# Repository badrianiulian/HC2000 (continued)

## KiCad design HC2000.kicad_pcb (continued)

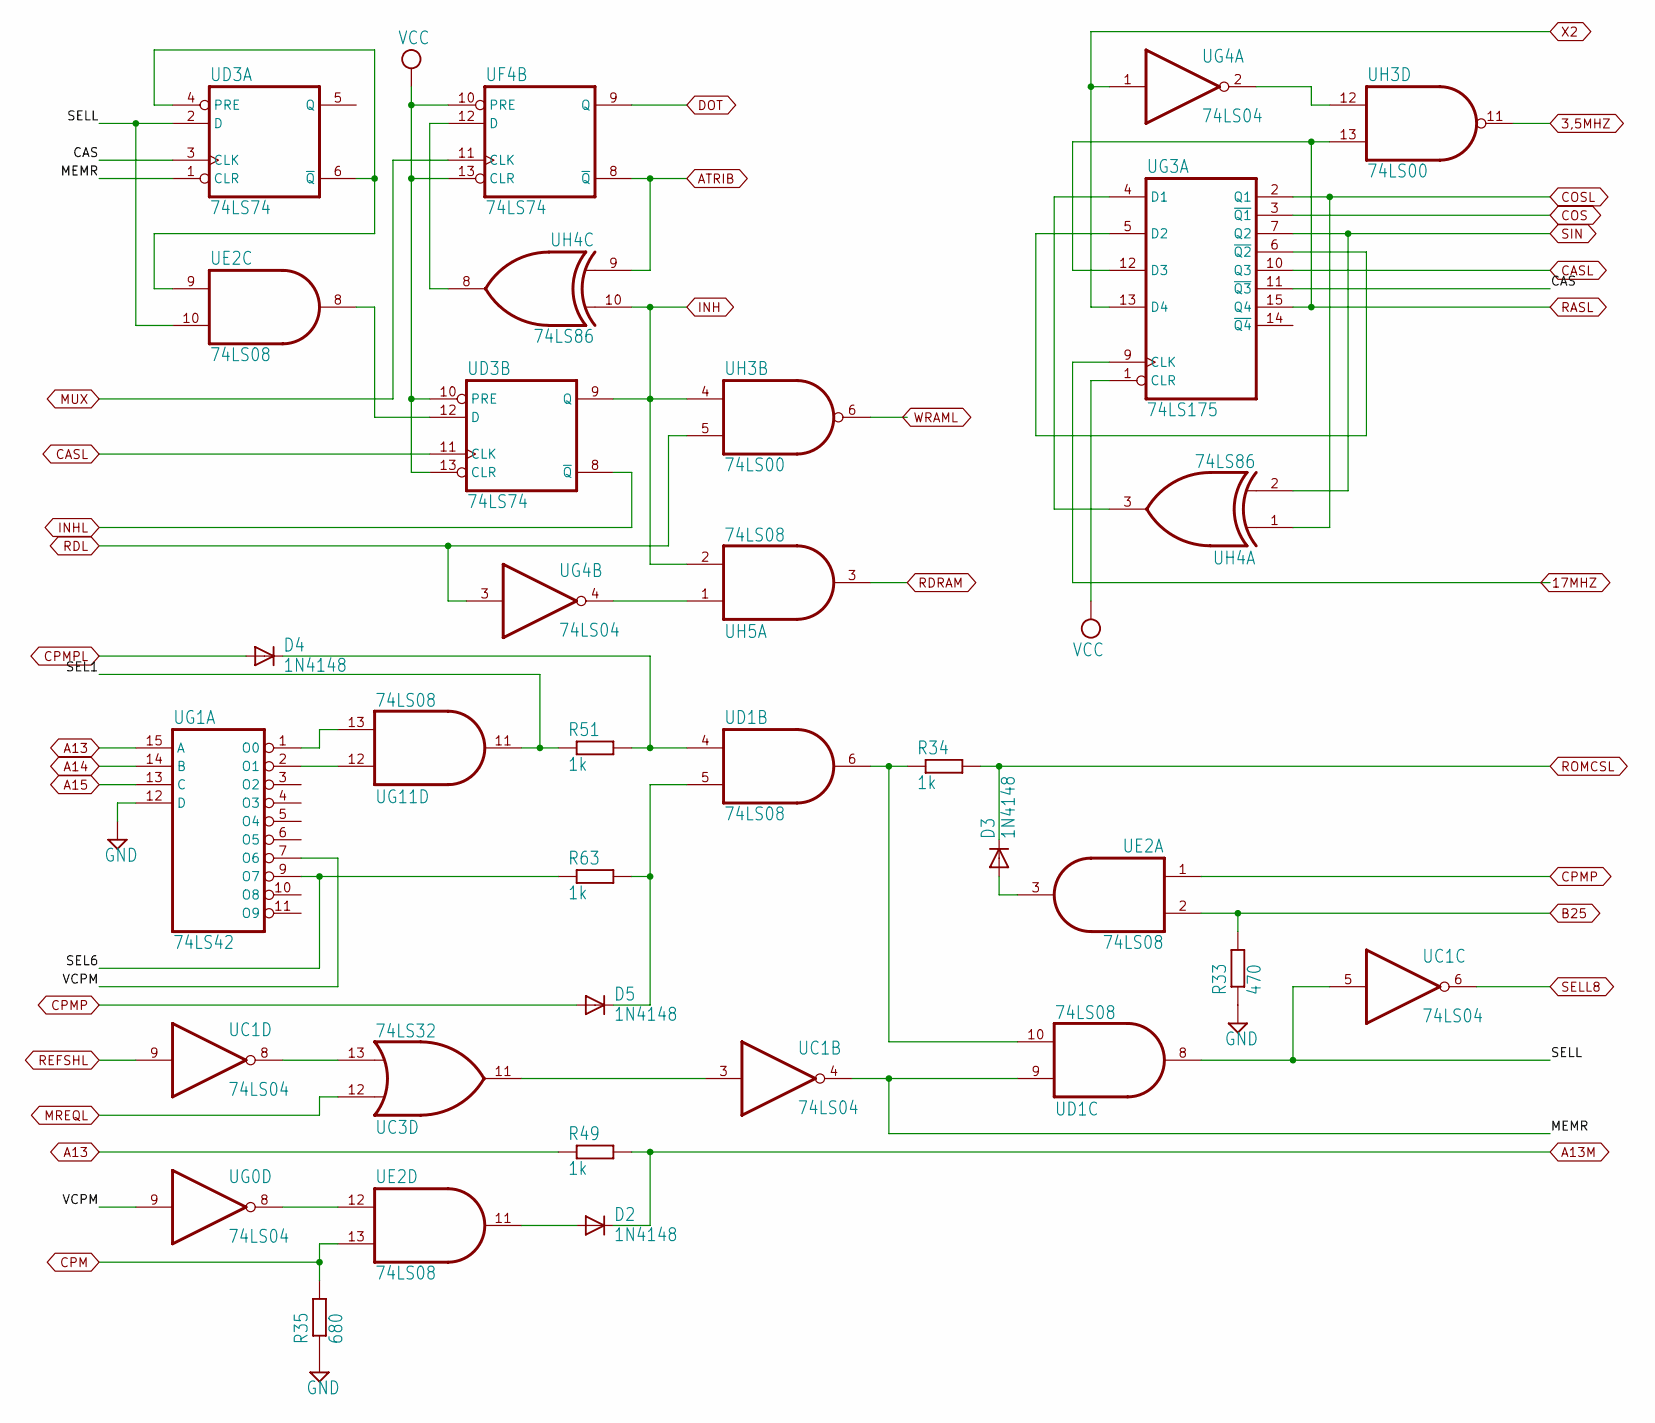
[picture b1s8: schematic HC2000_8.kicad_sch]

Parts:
D2, D3, D4, D5: 1N4148; DO35-10
R33: 470; 0204_7
R34, R49, R51, R63: 1k; 0204_7
R35: 680; 0204_7
UC1: 74LS04; DIL14
UC3: 74LS32; DIL14
UD1: 74LS08; DIL14
UD3: 74LS74; DIL14
UE2: 74LS08; DIL14
UF4: 74LS74; DIL14
UG0, UG4: 74LS04; DIL14
UG1: 74LS42; DIL16
UG3: 74LS175; DIL16
UG11: 74LS08; DIL14
UH3: 74LS00; DIL14
UH4: 74LS86; DIL14
UH5: 74LS08; DIL14

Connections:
3,5MHZ: UH3.11 (O); also elsewhere on the board
17MHZ: UG3.9 (CLK); also elsewhere on the board
/HC2000_8/CAS: UD3.3 (CLK), UG3.11 (~Q3)
/HC2000_8/MEMR: UC1.4 (O), UD1.9 (I0), UD3.1 (CLR)
/HC2000_8/SEL1: R51.1, UG11.11 (O)
/HC2000_8/SEL6: R63.1, UG1.9 (O7)
/HC2000_8/SELL: UC1.5 (I), UD1.8 (O), UD3.2 (D), UE2.10 (I1)
/HC2000_8/VCPM: UG0.9 (I), UG1.7 (O6)
A13M: D2.C, R49.2; also elsewhere on the board
A15: UG1.13 (C); also elsewhere on the board
ATRIB: UF4.8 (~Q), UH4.9 (I0); also elsewhere on the board
B25: R33.2, UE2.2 (I1); also elsewhere on the board
CASL: UD3.11 (CLK), UG3.10 (Q3); also elsewhere on the board
CPM: R35.2, UE2.13 (I1); also elsewhere on the board
CPMP: D5.A, UE2.1 (I0); also elsewhere on the board
CPMPL: D4.A; also elsewhere on the board
DOT: UF4.9 (Q); also elsewhere on the board
INH: UD3.9 (Q), UH3.4 (I0), UH4.10 (I1), UH5.2 (I1); also elsewhere on the board
INHL: UD3.8 (~Q); also elsewhere on the board
MUX: UF4.11 (CLK); also elsewhere on the board
unnamed: UC1.3 (I), UC3.11 (O)
unnamed: UC1.8 (O), UC3.13 (I1)
unnamed: D4.C, R51.2, UD1.4 (I0)
unnamed: D5.C, R63.2, UD1.5 (I1)
unnamed: R34.1, UD1.6 (O), UD1.10 (I1)
unnamed: UD3.4 (PRE), UD3.6 (~Q), UE2.9 (I0)
unnamed: UD3.12 (D), UE2.8 (O)
unnamed: D3.A, UE2.3 (O)
unnamed: UE2.12 (I0), UG0.8 (O)
unnamed: D2.A, UE2.11 (O)
unnamed: UF4.12 (D), UH4.8 (O)
unnamed: UG3.4 (D1), UH4.3 (O)
unnamed: UG3.5 (D2), UG3.6 (~Q2)
unnamed: UG4.2 (O), UH3.12 (I0)
unnamed: UG4.4 (O), UH5.1 (I0)
unnamed: UG1.2 (O1), UG11.12 (I0)
unnamed: UG1.1 (O0), UG11.13 (I1)
RASL: UG3.12 (D3), UG3.15 (Q4), UH3.13 (I1); also elsewhere on the board
RDL: UG4.3 (I), UH3.5 (I1); also elsewhere on the board
RDRAM: UH5.3 (O); also elsewhere on the board
REFSHL: UC1.9 (I); also elsewhere on the board
SELL8: UC1.6 (O); also elsewhere on the board
WRAML: UH3.6 (O); also elsewhere on the board
X2: UG3.13 (D4), UG4.1 (I); also elsewhere on the board

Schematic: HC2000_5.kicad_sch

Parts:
C6: -; C025-030X050
R36: 100; 0204_7
UC4, UC5: 74LS257; DIL16
UC7: 74LS244; DIL20
UD5: 74LS257; DIL16
UD7: TMM41464AP-12; DIL18
UE2: 74LS08; DIL14
UE3: 74LS32; DIL14
UE7: TMM41464AP-12; DIL18
UF3: 74LS175; DIL16
UG7: 74LS257; DIL16

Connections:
/HC2000_5/CVS: UD5.14 (4A), UF3.7 (Q2)
/HC2000_5/VMA0: UC5.4 (1Y), UD7.14 (A0), UE7.14 (A0), UG7.9 (3Y)
/HC2000_5/VMA1: UC5.9 (3Y), UD7.13 (A1), UE7.13 (A1), UG7.4 (1Y)
/HC2000_5/VMA2: UC5.12 (4Y), UD7.12 (A2), UE7.12 (A2), UG7.7 (2Y)
/HC2000_5/VMA3: UC5.7 (2Y), UD7.11 (A3), UE7.11 (A3), UG7.12 (4Y)
/HC2000_5/VMA4: UC4.9 (3Y), UD5.9 (3Y), UD7.8 (A4), UE7.8 (A4)
/HC2000_5/VMA5: UC4.7 (2Y), UD5.4 (1Y), UD7.7 (A5), UE7.7 (A5)
/HC2000_5/VMA6: UC4.4 (1Y), UD5.7 (2Y), UD7.6 (A6), UE7.6 (A6)
/HC2000_5/VMA7: UC4.12 (4Y), UD5.12 (4Y), UD7.10 (A7), UE7.10 (A7)
A: UD5.13 (4B); also elsewhere on the board
A13M: UC4.2 (1A); also elsewhere on the board
A15: UC4.14 (4A); also elsewhere on the board
B: UD5.6 (2B); also elsewhere on the board
C: UD5.11 (3A); also elsewhere on the board
CASL: UD7.16 (~CAS), UE7.16 (~CAS); also elsewhere on the board
CPMP: UF3.3 (~Q1); also elsewhere on the board
CPMPL: UF3.2 (Q1); also elsewhere on the board
D: UD5.3 (1B); also elsewhere on the board
D4: UC7.17 (A4); also elsewhere on the board
D5: UC7.15 (A3); also elsewhere on the board
D6: UC7.11 (A1); also elsewhere on the board
D7: UC7.13 (A2); also elsewhere on the board
IG3: UG7.2 (1A); also elsewhere on the board
IG4: UG7.5 (2A); also elsewhere on the board
IG5: UG7.11 (3A); also elsewhere on the board
INH: UD5.15 (G), UG7.15 (G); also elsewhere on the board
INHL: UC4.15 (G), UC5.15 (G); also elsewhere on the board
MUX: UC4.1 (~A/B), UC5.1 (~A/B), UD5.1 (~A/B), UE2.6 (O), UG7.1 (~A/B); also elsewhere on the board
unnamed: C6.1, R36.1, UE2.4 (I0), UE2.5 (I1)
unnamed: UE3.4 (I0), UF3.15 (Q4)
unnamed: UE3.6 (O), UF3.9 (CLK)
OUT7EL: UE3.5 (I1); also elsewhere on the board
RASL: R36.2, UD7.5 (~RAS), UE7.5 (~RAS); also elsewhere on the board
RESETL: UF3.1 (CLR); also elsewhere on the board
VD0: UC7.16 (Y2), UD7.2 (I/O1); also elsewhere on the board
VD1: UC7.14 (Y3), UD7.3 (I/O2); also elsewhere on the board
VD2: UC7.12 (Y4), UD7.15 (I/O3); also elsewhere on the board
VD3: UC7.18 (Y1), UD7.17 (I/O4); also elsewhere on the board
VD4: UC7.3 (Y4), UE7.2 (I/O1); also elsewhere on the board
VD5: UC7.5 (Y3), UE7.3 (I/O2); also elsewhere on the board
VD6: UC7.9 (Y1), UE7.15 (I/O3); also elsewhere on the board
VD7: UC7.7 (Y2), UE7.17 (I/O4); also elsewhere on the board
WRAML: UC7.1 (G), UC7.19 (G), UD7.4 (~WE), UE7.4 (~WE); also elsewhere on the board
X3Y7: UD5.2 (1A); also elsewhere on the board
X5: UG7.10 (3B); also elsewhere on the board
X6: UG7.3 (1B); also elsewhere on the board
X7: UG7.6 (2B); also elsewhere on the board
X8: UG7.13 (4B); also elsewhere on the board
X9: UD5.10 (3B); also elsewhere on the board

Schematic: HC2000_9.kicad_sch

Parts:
R26, R42, R45: -; 0204_7
R28, R37, R38, R40, R41: 1k; 0204_7
UA11: 74LS06; DIL14
UB12: 74LS153; DIL16
UC12: 74LS175; DIL16
UD11: 74LS14; DIL14
UE8: 8272 or D765AC-2; DIL40
UG11: 74LS08; DIL14

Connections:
CLK8272: UC12.9 (CLK), UE8.19 (CLK); also elsewhere on the board
CS8272: UE8.4 (NCS); also elsewhere on the board
D4: UE8.10 (D4); also elsewhere on the board
D5: UE8.11 (D5); also elsewhere on the board
D6: UE8.12 (D6); also elsewhere on the board
D7: UE8.13 (D7); also elsewhere on the board
DIR: UA11.8 (O); also elsewhere on the board
DWIN: UE8.22 (DW); also elsewhere on the board
FRDATA: UE8.23 (RDDATA); also elsewhere on the board
unnamed: UA11.3 (I), UC12.2 (Q1)
unnamed: UA11.5 (I), UC12.1 (CLR), UE8.25 (WE)
unnamed: UA11.9 (I), UB12.9 (2Y)
unnamed: UA11.11 (I), UG11.8 (O)
unnamed: UA11.13 (I), UE8.27 (HDSEL)
unnamed: UB12.6 (1C0), UC12.5 (D2), UC12.10 (Q3)
unnamed: UB12.5 (1C1), UC12.12 (D3), UC12.15 (Q4)
unnamed: UB12.4 (1C2), UC12.7 (Q2)
unnamed: UB12.7 (1Y), UC12.4 (D1)
unnamed: UB12.10 (2C0), UB12.11 (2C1), UB12.12 (2C2), UB12.13 (2C3), UE8.38 (LCT/DIR)
unnamed: UB12.14 (A), UE8.32 (PS0)
unnamed: UB12.2 (B), UE8.31 (PS1)
unnamed: UC12.13 (D4), UE8.30 (WRDATA)
unnamed: UD11.8 (O), UE8.34 (WP/TS)
unnamed: UD11.6 (O), UG11.4 (I0)
unnamed: UE8.33 (FLT/TRK00), UG11.6 (O)
unnamed: UE8.37 (FR/STP), UG11.10 (I1)
unnamed: R38.1, UE8.15 (NDACK)
unnamed: UE8.39 (NRW/SEEK), UG11.5 (I1), UG11.9 (I0)
unnamed: R37.1, UE8.35 (RDY)
PROT: R26.2, R28.1, UD11.9 (I); also elsewhere on the board
RD8272: UE8.2 (NRD); also elsewhere on the board
RES8272: UE8.1 (RST); also elsewhere on the board
SIDE: UA11.12 (O); also elsewhere on the board
STEP: UA11.10 (O); also elsewhere on the board
TC: UE8.16 (TC); also elsewhere on the board
TRACK0: R40.1, R45.2, UD11.5 (I); also elsewhere on the board
VCO: UE8.24 (VCO); also elsewhere on the board
WR8272: UE8.3 (NWR); also elsewhere on the board
WRCLK: UE8.21 (WRCLK); also elsewhere on the board
WRDATA: UA11.4 (O); also elsewhere on the board
WREN: UA11.6 (O); also elsewhere on the board

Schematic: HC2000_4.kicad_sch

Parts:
C5, C11: 270p; C025-030X050
R19, R19B0: 470; 0204_7
UB1: 74LS74; DIL14
UB2: 74LS00; DIL14
UC2: 74LS27; DIL14
UC3: 74LS32; DIL14
UD1: 74LS08; DIL14
UE3: 74LS32; DIL14
UF4: 74LS74; DIL14
UH4: 74LS86; DIL14

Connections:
/HC2000_4/BLANKH: UB1.9 (Q), UC2.11 (I2), UD1.1 (I0)
/HC2000_4/HSYNCL: UB1.13 (CLR), UC3.3 (O), UD1.12 (I0), UH4.12 (I0)
BLANK: UD1.3 (O); also elsewhere on the board
BORD: UF4.5 (Q); also elsewhere on the board
HSYNC: UB1.3 (CLK), UB1.8 (~Q), UD1.13 (I1); also elsewhere on the board
IG0: UC2.9 (I0); also elsewhere on the board
IG1: UC2.10 (I1); also elsewhere on the board
IG2: UC2.5 (I2); also elsewhere on the board
IG4: UC2.4 (I1); also elsewhere on the board
IG5: UE3.9 (I0); also elsewhere on the board
IG6: UB2.5 (I1); also elsewhere on the board
IG7: UB2.4 (I0); also elsewhere on the board
IG8: UE3.10 (I1); also elsewhere on the board
INTL: R19.2; also elsewhere on the board
unnamed: UB1.2 (D), UB1.6 (~Q)
unnamed: UB1.12 (D), UC3.1 (I0), UC3.6 (O)
unnamed: UB2.6 (O), UB2.9 (I0)
unnamed: R19B0.1, UB2.8 (O)
unnamed: UB2.12 (I0), UC2.8 (O)
unnamed: R19.1, UB2.11 (O)
unnamed: UC2.3 (I0), UD1.2 (I1), UE3.8 (O)
unnamed: C11.1, R19B0.2, UF4.2 (D)
SHVL: UH4.11 (O); also elsewhere on the board
VSYNCL: UB2.13 (I1), UC2.6 (O), UH4.13 (I1); also elsewhere on the board
X4L: UF4.3 (CLK); also elsewhere on the board
X6: UB1.11 (CLK); also elsewhere on the board
X7: C5.2, UC3.2 (I1); also elsewhere on the board
X8: UC3.5 (I1); also elsewhere on the board
X10: UB2.10 (I1), UC3.4 (I0); also elsewhere on the board

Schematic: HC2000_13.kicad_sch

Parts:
C10: 270p; C025-024X044
Q2: 8MHz; HC18U-H
R39, R57: 560; 0204_7
R56: 1k; 0204_7
UD11: 74LS14; DIL14
UD12: 74LS161; DIL16
UE11: 74LS04; DIL14
UG11: 74LS08; DIL14
UG12: 74LS74; DIL14
UH11: 74LS93; DIL14
UH12: 74LS74; DIL14

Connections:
CLK8272: UD12.2 (CLK), UE11.9 (I), UH11.1 (CKB), UH11.12 (QA), UH12.3 (CLK); also elsewhere on the board
DWIN: UD12.6 (P4), UD12.11 (Q4); also elsewhere on the board
FRDATA: UG12.5 (Q); also elsewhere on the board
unnamed: UD11.4 (O), UH12.11 (CLK)
unnamed: UD12.9 (LD), UG12.6 (~Q), UH12.13 (CLR)
unnamed: Q2.1, R57.1, UE11.3 (I)
unnamed: C10.+, R57.2, UE11.4 (O)
unnamed: C10.-, R39.1, UE11.5 (I)
unnamed: Q2.2, R39.2, UE11.6 (O), UH11.14 (CKA)
unnamed: UE11.8 (O), UG12.3 (CLK)
unnamed: UG11.1 (I0), UH11.8 (QC)
unnamed: UG11.2 (I1), UH11.11 (QD)
unnamed: UG11.3 (O), UH12.1 (CLR)
unnamed: UG12.2 (D), UH12.9 (Q)
unnamed: UH12.2 (D), UH12.6 (~Q)
RDDATA: R56.2, UD11.3 (I); also elsewhere on the board
VCO: UD12.1 (~CL), UG12.1 (CLR); also elsewhere on the board
WRCLK: UH12.5 (Q); also elsewhere on the board

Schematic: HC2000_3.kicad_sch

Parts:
UC3: 74LS32; DIL14
UD4: 74LS157; DIL16
UE5: 74LS161; DIL16
UF2, UF5: 74LS161; DIL16
UG4: 74LS04; DIL14
UG5: 74LS161; DIL16
UH3: 74LS00; DIL14
UH7: 74LS161; DIL16

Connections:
3,5MHZ: UF2.7 (PE); also elsewhere on the board
17MHZ: UF2.2 (CLK); also elsewhere on the board
/HC2000_3/TC1: UE5.2 (CLK), UF2.15 (CO), UF5.2 (CLK), UG4.11 (I), UG5.2 (CLK), UH7.2 (CLK)
/HC2000_3/TCUC: UF5.7 (PE), UF5.10 (TE), UH3.10 (I1), UH7.15 (CO)
/HC2000_3/X4: UF2.11 (Q4), UG4.13 (I)
A: UD4.9 (3Y); also elsewhere on the board
B: UD4.4 (1Y); also elsewhere on the board
C: UD4.12 (4Y); also elsewhere on the board
D: UD4.7 (2Y); also elsewhere on the board
DOT: UC3.9 (I0), UD4.1 (~A/B); also elsewhere on the board
IG0: UD4.5 (2A), UF5.12 (Q3); also elsewhere on the board
IG1: UD4.2 (1A), UF5.11 (Q4); also elsewhere on the board
IG2: UD4.11 (3A), UE5.14 (Q1); also elsewhere on the board
IG3: UE5.13 (Q2); also elsewhere on the board
IG4: UE5.12 (Q3); also elsewhere on the board
IG5: UE5.11 (Q4); also elsewhere on the board
IG6: UD4.6 (2B), UD4.14 (4A), UG5.14 (Q1); also elsewhere on the board
IG7: UC3.10 (I1), UD4.3 (1B), UG5.13 (Q2); also elsewhere on the board
IG8: UG5.12 (Q3); also elsewhere on the board
unnamed: UE5.15 (CO), UG5.3 (P1), UG5.4 (P2), UG5.6 (P4), UG5.7 (PE), UG5.10 (TE)
unnamed: UE5.9 (LD), UG4.8 (O), UG5.9 (LD)
unnamed: UE5.4 (P2), UE5.7 (PE), UE5.10 (TE), UF5.15 (CO)
unnamed: UF2.14 (Q1), UG4.5 (I)
unnamed: UG4.9 (I), UG5.15 (CO)
unnamed: UH3.8 (O), UH7.9 (LD)
TC1L: UG4.10 (O); also elsewhere on the board
X1L: UG4.6 (O); also elsewhere on the board
X2: UF2.13 (Q2); also elsewhere on the board
X3Y7: UC3.8 (O); also elsewhere on the board
X4L: UG4.12 (O); also elsewhere on the board
X5: UH7.14 (Q1); also elsewhere on the board
X6: UH7.13 (Q2); also elsewhere on the board
X7: UH7.12 (Q3); also elsewhere on the board
X8: UH7.11 (Q4); also elsewhere on the board
X9: UF5.14 (Q1), UH3.9 (I0); also elsewhere on the board
X10: UF5.13 (Q2), UH7.3 (P1), UH7.4 (P2), UH7.5 (P3); also elsewhere on the board

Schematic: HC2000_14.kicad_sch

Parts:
CD1, CD6, CD9, CD11, CD13, CD15, CD16, CD17, CD19, CD20, CD21, CD22, CD24, CD25, CD26, CD27, CD30, CD31, CD32, CD33, CD35, CD36, CD37, CD39, CD40: u1; C025-024X044
CD2, CD4, CD7, CD8, CD10, CD14, CD28, CD29, CD34, CD38: -; C025-024X044
CD3, CD5, CD12, CD18, CD23: 100u; C025-024X044
CX0: 100u; C025-024X044
J1: VIDEO; DSUB-9_Female_Horizontal_P2.77x2.84mm_EdgePinOffset7.70mm_H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
J2: JOYSTICK; DSUB-9_Male_Horizontal_P2.77x2.84mm_EdgePinOffset7.70mm_Hou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
J3: Mic_Jack; Tayda_3.5mm_stereo_TRS_jack_A-853
J4, J10: Jack-DC; BarrelJack_Wuerth_6941xx301002
J5: RS232 + RETEA; DSUB-9_Female_Horizontal_P2.77x2.84mm_EdgePinOffset7.70mm_H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
J6: .; HC-POWER
J7, J8: FDD-CON; 2X17
J9: .; 10X04MTA
J12: Ear_Jack; Tayda_3.5mm_stereo_TRS_jack_A-853
JP2: -; JP1
PS1: DD1718PA
SW1: RESET_SW
UA1: 74LS244; DIL20
Z1: HCBUS; HC_Bus_Edge_Connector

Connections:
+5V: J7.5, J7.6, J8.5, J8.6
+12V: J6.4, J7.1, J7.2, J8.1, J8.2, PS1.3 (+Vo); also elsewhere on the board
-12V: J6.3, PS1.5 (-Vo); also elsewhere on the board
A15: Z1.A1 (A15); also elsewhere on the board
B25: Z1.B25 (~ROMCS); also elsewhere on the board
BUSAKL: Z1.B26 (~BUSACK); also elsewhere on the board
BUSRQL: Z1.B19 (~BUSRQ); also elsewhere on the board
CASL: Z1.B8 (CLK); also elsewhere on the board
CPM: Z1.B4 (+9V); also elsewhere on the board
CTS: J5.1; also elsewhere on the board
D4: Z1.A12 (D4); also elsewhere on the board
D5: Z1.A10 (D5); also elsewhere on the board
D6: Z1.A9 (D6); also elsewhere on the board
D7: Z1.A3 (D7); also elsewhere on the board
DIR: J7.18, J8.18; also elsewhere on the board
DS0: J7.10, J7.14, J8.12, J8.16; also elsewhere on the board
DS1: J7.12, J7.16, J8.10, J8.14; also elsewhere on the board
DTR: J5.2; also elsewhere on the board
EAR: J12.4, J12.5; also elsewhere on the board
HALTL: Z1.A15 (~HALT); also elsewhere on the board
HSYNC: UA1.2 (A1); also elsewhere on the board
INTL: Z1.A13 (~INT); also elsewhere on the board
IORQE: Z1.B13 (~IORQGE); also elsewhere on the board
IORQL: Z1.A17 (~IORQ); also elsewhere on the board
M1L: Z1.A24 (~M1); also elsewhere on the board
MBRIGHT: UA1.17 (A4); also elsewhere on the board
MIC: J3.4, J3.5; also elsewhere on the board
NET: J5.5; also elsewhere on the board
NMIL: Z1.A14 (~NMI); also elsewhere on the board
unnamed: J1.8, UA1.18 (Y1)
unnamed: J1.4, UA1.16 (Y2)
unnamed: J1.5, UA1.14 (Y3)
unnamed: J1.9, UA1.12 (Y4)
unnamed: J1.3, UA1.7 (Y2)
unnamed: J1.1, UA1.5 (Y3)
unnamed: J1.6, UA1.3 (Y4)
PROT: J7.28, J8.28; also elsewhere on the board
RDDATA: J7.30, J8.30; also elsewhere on the board
RDL: Z1.A18 (~RD); also elsewhere on the board
REFSHL: Z1.A25 (~RFSH); also elsewhere on the board
RESETL: SW1.2, Z1.B20 (~RESET); also elsewhere on the board
RXD: J5.3; also elsewhere on the board
SHVL: UA1.15 (A3); also elsewhere on the board
SIDE: J7.32, J8.32; also elsewhere on the board
STEP: J7.20, J8.20; also elsewhere on the board
TA11: J2.7; also elsewhere on the board
TA12: J2.8; also elsewhere on the board
TD0: J2.4; also elsewhere on the board
TD1: J2.3; also elsewhere on the board
TD2: J2.9; also elsewhere on the board
TD3: J2.2; also elsewhere on the board
TD4: J2.1; also elsewhere on the board
TRACK0: J7.26, J8.26; also elsewhere on the board
TXD: J5.4; also elsewhere on the board
VIDEO: J1.7, J9.1, J9.4; also elsewhere on the board
VSYNCL: UA1.8 (A4); also elsewhere on the board
WAITL: Z1.A21 (~WAIT); also elsewhere on the board
WRDATA: J7.22, J8.22; also elsewhere on the board
WREN: J7.24, J8.24; also elsewhere on the board
WRL: Z1.A19 (~WR); also elsewhere on the board

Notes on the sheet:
CAS-DIN

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
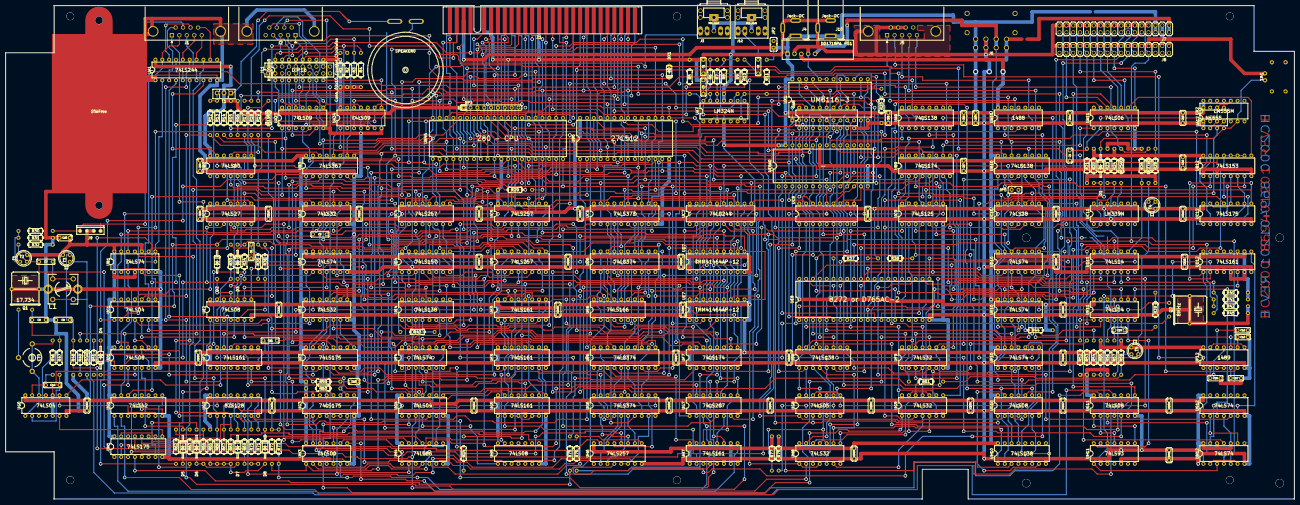
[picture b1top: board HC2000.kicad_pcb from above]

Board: 2 copper layers, 478.0 x 183.0 mm, 263 parts (0 on the bottom side), 371 nets.

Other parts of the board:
SilkFree: SilkFree

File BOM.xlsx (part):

Source: | /Volumes/8TB1/Z80/HC/HC-2000/HC2000-GIT/HC2000.kicad_sch
Date: | 2023 July 23, Sunday 23:11:08
Tool: | Eeschema 7.0.1-0
Generator: | /Applications/KiCad/KiCad.app/Contents/SharedSupport/plugins/bom_csv_grouped_by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
Component Count: | 264
Collated Components:
Item | Qty | Reference(s) | Value | LibPart | Footprint | Datasheet | DNP | Alt | Sim.Device | Sim.Pins
1 | 2 | C1, C3 | 100n | HC2000:C-EU025-025X050 | HC2000:C025-030X050
2 | 1 | C2 | 4n7 | HC2000:C-EU025-030X050 | HC2000:C025-030X050
3 | 1 | C4 | 4,7uF | HC2000:CPOL-EU140CLH-0810 | HC2000:C025-024X044
4 | 2 | C5, C11 | 270p | HC2000:C-EU025-030X050 | HC2000:C025-030X050
5 | 2 | C6, C8 | - | HC2000:C-EU025-025X050 | HC2000:C025-030X050
6 | 1 | C7 | 15p | HC2000:C-EU025-025X050 | HC2000:C025-030X050
7 | 1 | C9 | 220p | HC2000:C-EU025-025X050 | HC2000:C025-030X050
8 | 1 | C10 | 270p | HC2000:C-EU025-024X044 | HC2000:C025-024X044
9 | 4 | C12, C13, C16, C17 | 4n7 | HC2000:C-EU025-025X050 | HC2000:C025-025X050
10 | 1 | C14 | 180p | HC2000:C-EU025-025X050 | HC2000:C025-030X050
11 | 1 | C15 | 10u | HC2000:CPOL-EU140CLH-1010 | HC2000:C025-024X024
12 | 25 | CD1, CD6, CD9, CD11, CD13, CD15, CD16, CD17, CD19, CD20, CD21, CD22, CD24, CD25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 | u1 | HC2000:C-EU025-024X044 | HC2000:C025-024X044
13 | 10 | CD2, CD4, CD7, CD8, CD10, CD14, CD28, CD29, CD34, CD38 | - | HC2000:C-EU025-024X044 | HC2000:C025-024X044
14 | 5 | CD3, CD5, CD12, CD18, CD23 | 100u | HC2000:C-EU025-024X044 | HC2000:C025-024X044
15 | 1 | CT0 | 10-60pF | HC2000:C-TRIMM808 | HC2000:CTRIM808-BC
16 | 1 | CX0 | 100u | HC2000:CPOL-EU140CLH-0810 | HC2000:C025-024X044
17 | 1 | CY1 | 1.5u | HC2000:CPOL-EU140CLH-1010 | HC2000:140CLH-1010
18 | 8 | D1, D2, D3, D4, D5, D6, D7, D8 | 1N4148 | HC2000:1N4148DO35-10 | HC2000:DO35-10
19 | 1 | DX1 | 1N4148 | HC2000:1N4148DO35-7 | HC2000:DO35-7 | https://assets.nexperia.com/documents/data-sheet/1N4148_1N4448.pdf |  |  | D | 1=K 2=A
20 | 1 | J1 | VIDEO | HC2000:F09FD | HC2000:DSUB-9_Female_Horizontal_P2.77x2.84mm_EdgePinOffset7.70mm_Housed_Mountin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
21 | 1 | J2 | JOYSTICK | HC2000:F09MD | HC2000:DSUB-9_Male_Horizontal_P2.77x2.84mm_EdgePinOffset7.70mm_Housed_MountingH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
22 | 1 | J3 | Mic_Jack | HC2000:Audio-Jack-3_2Switches | HC2000:Tayda_3.5mm_stereo_TRS_jack_A-853 | ~
23 | 2 | J4, J10 | Jack-DC | HC2000:Jack-DC | HC2000:BarrelJack_Wuerth_6941xx301002 | ~
24 | 1 | J5 | RS232 + RETEA | HC2000:F09FD | HC2000:DSUB-9_Female_Horizontal_P2.77x2.84mm_EdgePinOffset7.70mm_Housed_Mountin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
25 | 1 | J6 | . | HC2000:HC-POWER | HC2000:HC-POWER
26 | 2 | J7, J8 | FDD-CON | HC2000:PINHD-2X17 | HC2000:2X17
27 | 1 | J9 | . | HC2000:MTA04-100 | HC2000:10X04MTA
28 | 1 | J11 | Conn_02x10_Counter_Clockwise | HC2000:Conn_02x10_Counter_Clockwise | HC2000:PinHeader_2x10_P2.54mm_Vertical | ~
29 | 1 | J12 | Ear_Jack | HC2000:Audio-Jack-3_2Switches | HC2000:Tayda_3.5mm_stereo_TRS_jack_A-853 | ~
30 | 2 | JP2, JP5 | - | HC2000:JP1E | HC2000:JP1
31 | 1 | JX1 | OPEN with 1 EPROM | HC2000:SolderJumper_2_Open | HC2000:SolderJumper-2_P1.3mm_Open_Pad1.0x1.5mm | ~
32 | 3 | JX2, JX3, JX4 | CLOSED with 1 EPROM | HC2000:SolderJumper_2_Open | HC2000:SolderJumper-2_P1.3mm_Open_Pad1.0x1.5mm | ~
33 | 1 | KB-CONN0 | DIP16 | HC2000:DIL16 | HC2000:DIL16
34 | 1 | L1 | 100mH | HC2000:L-USPIS2816 | HC2000:PIS2816
35 | 1 | PS1 | DD1718PA | HC2000:DD1718PA | HC2000:DD1718PA
36 | 1 | Q1 | 17.734000000000002 | HC2000:CRYSTALHC18U-H | HC2000:HC18U-H
37 | 1 | Q2 | 8MHz | HC2000:CRYSTALHC18U-H | HC2000:HC18U-H
38 | 28 | R1, R2, R3, R4, R13, R14, R28, R34, R37, R38, R40, R41, R44, R47, R49, R51, R53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 | 1k | HC2000:R-EU_0204{slash}7 | HC2000:0204_7
39 | 2 | R5, R60 | 300 | HC2000:R-EU_0204{slash}7 | HC2000:0204_7
40 | 1 | R6 | 2M | HC2000:R-EU_0204{slash}7 | HC2000:0204_7
41 | 11 | R7, R8, R9, R11, R15, R16, R18, R20, R25A0, R29, R52 | 10k | HC2000:R-EU_0204{slash}7 | HC2000:0204_7
42 | 1 | R10 | 47k | HC2000:R-EU_0204{slash}7 | HC2000:0204_7
43 | 2 | R12, R17 | 2k | HC2000:R-EU_0204{slash}7 | HC2000:0204_7
44 | 6 | R19, R19B0, R33, R43, R50A0, R62 | 470 | HC2000:R-EU_0204{slash}7 | HC2000:0204_7
45 | 1 | R21 | 470k | HC2000:R-EU_0204{slash}7 | HC2000:0204_7
46 | 1 | R22 | 6k | HC2000:R-EU_0204{slash}7 | HC2000:0204_7
47 | 1 | R23 | 220 | HC2000:R-EU_0204{slash}7 | HC2000:0204_7
48 | 1 | R24 | 430 | HC2000:R-EU_0204{slash}7 | HC2000:0204_7
49 | 3 | R26, R42, R45 | - | HC2000:R-EU_0204{slash}7 | HC2000:0204_7
50 | 1 | R27A0 | 47 | HC2000:R-EU_0204{slash}7 | HC2000:0204_7
51 | 2 | R30, R48 | 69 | HC2000:R-EU_0204{slash}7 | HC2000:0204_7
52 | 1 | R31 | 270 | HC2000:R-EU_0204{slash}7 | HC2000:0204_7
53 | 1 | R32 | 1k5 | HC2000:R-EU_0204{slash}7 | HC2000:0204_7
54 | 1 | R35 | 680 | HC2000:R-EU_0204{slash}7 | HC2000:0204_7
55 | 1 | R36 | 100 | HC2000:R-EU_0204{slash}7 | HC2000:0204_7
56 | 3 | R39, R46, R57 | 560 | HC2000:R-EU_0204{slash}7 | HC2000:0204_7
57 | 2 | R54, R61 | 3k9 | HC2000:R-EU_0204{slash}7 | HC2000:0204_7
58 | 1 | R59 | 27k | HC2000:R-EU_0204{slash}7 | HC2000:0204_7
59 | 1 | R64 | 7k5 | HC2000:R-EU_0204{slash}7 | HC2000:0204_7
60 | 2 | R65, R71 | 510 | HC2000:R-EU_0204{slash}7 | HC2000:0204_7
61 | 1 | R66 | 1k6 | HC2000:R-EU_0204{slash}7 | HC2000:0204_7
62 | 1 | R67 | 910 | HC2000:R-EU_0204{slash}7 | HC2000:0204_7
63 | 1 | R68 | 5k1 | HC2000:R-EU_0204{slash}7 | HC2000:0204_7
64 | 1 | R69 | 2k7 | HC2000:R-EU_0204{slash}7 | HC2000:0204_7
65 | 1 | R70 | 1k1 | HC2000:R-EU_0204{slash}7 | HC2000:0204_7
66 | 1 | RP1 | 10k | HC2000:G08R | HC2000:SIL9
67 | 1 | SPEAKER0 | BEL | HC2000:AL11P | HC2000:AL11P
68 | 1 | SW1 | RESET_SW | HC2000:RESET_SW | HC2000:RESET_SW | ~
69 | 1 | T1 | BD139 | HC2000:BD139 | HC2000:TO-126-3_Vertical
70 | 1 | T2 | 2N2368 | HC2000:2N2369 | HC2000:TO18
71 | 1 | T3 | BC108A | HC2000:2N2369 | HC2000:TO18
72 | 2 | T4, T5 | BC177 | HC2000:BC177 | HC2000:TO18
73 | 2 | UA1, UC7 | 74LS244 | HC2000:74244N | HC2000:DIL20
74 | 1 | UA7 | LM324N | HC2000:LM324N | HC2000:DIL14
75 | 2 | UA8, UC8 | - | HC2000:2114 | HC2000:DIL18
76 | 5 | UA9, UB10, UE4, UF8, UH10 | 74LS138 | HC2000:74138N | HC2000:DIL16
77 | 1 | UA10 | 1488 | HC2000:DIL14 | HC2000:DIL14 |  |  | 75188
78 | 1 | UA11 | 74LS06 | HC2000:7406N | HC2000:DIL14
79 | 1 | UA12 | NE555 | HC2000:NE555 | HC2000:DIL-08
80 | 2 | UA23, UA34 | 74LS09 | HC2000:7409N | HC2000:DIL14
81 | 8 | UB1, UD3, UD10, UE10, UF4, UF10, UG12, UH12 | 74LS74 | HC2000:7474N | HC2000:DIL14
82 | 2 | UB2, UH3 | 74LS00 | HC2000:7400N | HC2000:DIL14
83 | 1 | UB3 | 74LS367 | HC2000:74367N | HC2000:DIL16
84 | 1 | UB6 | 27C512 | HC2000:27256 | HC2000:DIL28
85 | 2 | UB9, UF7 | 74LS174 | HC2000:74174N | HC2000:DIL16
86 | 1 | UB12 | 74LS153 | HC2000:74153N | HC2000:DIL16
87 | 1 | UB45 | Z80 - CPU | HC2000:Z80CPU | HC2000:DIL40
88 | 4 | UC1, UE11, UG0, UG4 | 74LS04 | HC2000:7404N | HC2000:DIL14
89 | 1 | UC2 | 74LS27 | HC2000:7427N | HC2000:DIL14
90 | 5 | UC3, UE3, UF9, UG9, UH8 | 74LS32 | HC2000:7432N | HC2000:DIL14
91 | 5 | UC4, UC5, UD5, UG7, UH6 | 74LS257 | HC2000:74257N | HC2000:DIL16
92 | 1 | UC6 | 74LS373 | HC2000:74373N | HC2000:DIL20
93 | 1 | UC9 | 74LS125 | HC2000:74125N | HC2000:DIL14
94 | 1 | UC10 | 74LS38 | HC2000:7403N | HC2000:DIL14
95 | 1 | UC11 | LM339N | HC2000:LM339N | HC2000:DIL14
96 | 4 | UC12, UF3, UG3, UH1 | 74LS175 | HC2000:74175N | HC2000:DIL16
97 | 5 | UD1, UE2, UG10, UG11, UH5 | 74LS08 | HC2000:7408N | HC2000:DIL14
98 | 1 | UD4 | 74LS157 | HC2000:74157N | HC2000:DIL16
99 | 3 | UD6, UF6, UG6 | 74LS374 | HC2000:74374N | HC2000:DIL20
100 | 2 | UD7, UE7 | TMM41464AP-12 | HC2000:41464C | HC2000:DIL18
101 | 1 | UD11 | 74LS14 | HC2000:7414N | HC2000:DIL14
102 | 6 | UD12, UE5, UF2, UF5, UG5, UH7 | 74LS161 | HC2000:4161P | HC2000:DIL16
103 | 1 | UE6 | 74LS166 | HC2000:74166N | HC2000:DIL16
104 | 1 | UE8 | 8272 or D765AC-2 | HC2000:8272 | HC2000:DIL40
105 | 1 | UE8A0 | - | HC2000:27128P | HC2000:DIL28-6
106 | 1 | UF12 | 1489 | HC2000:DIL14 | HC2000:DIL14 |  |  | 75189
107 | 1 | UG1 | 74LS42 | HC2000:7442N | HC2000:DIL16
108 | 1 | UG2 | 82S128 | HC2000:DIL16 | HC2000:DIL16
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
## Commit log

2023-04-25 Updated ICs values and positions
2023-04-25 IC Map for Rev E drawn on Rev B
2023-05-08 EPROM dump (RCT PRO)
2023-05-09 RCT PRO
2023-05-15 Original SCAN
2023-05-16 Fix errors (IC & unnoticed cut for 1 EPROM)
2023-05-16 Base Images
2023-05-16 Rebuilt BOM
2023-05-17 First Rev PCB Fixes
2023-05-17 Revision-E
2023-05-24 Case parts
2023-05-27 A few minor changes
    R62 has value 470 instead of 910 and C6 is missing.
    Connected a few conector's shield pins to GND.
2023-07-16 Serial fix. Thanks to svpantazi for testing
2023-07-16 Update README.md
    Serial fix. Thanks to svpantazi
2023-07-16 Revision E final fixes before fork
2023-07-23 Updated power, audio and keyboard connectors
